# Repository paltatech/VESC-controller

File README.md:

# 3 phase motor controller for high power systems
This is the hardware repository of a 3 phase inverter brain, UNTESTED but designed with the following specs in mind:

* Compatible with VESC firmware and software tools
* Embedded security features (overcurrent protection, pwm overlap elimination, etc)

## Microcontroller
The core of the system is a 32 bit ARM Cortex M4 MCU (STM32F405) running ChibiOS RTOS.

## Communication interfaces
* CAN bus for control, configuration and monitoring
* USB for light usage, firmware upload/upgrade and configuration.
* UART, I2C and ADCs and GPIOs available

## Motor inputs
* Bus Voltage (differential)
* Phase current (differential)
* Phase voltage (differential)
* Gate driver fault
* Power_good from gate driver
* Motor temperature
* Hall/encoder
* Resolver

## Gate driver outputs
* PWM high/low
* dynamic gate drive current (pwm)
* 24v power

You can also check the layout [here](https://eyrie.io/board/6f397be723754f039735d8350260c2c0) 

Made open source with KiCAD, an open source EDA tool.

## Interface boards
This controller can be interfaced directly to a power stage, or through an interface board.
An example of interface board is at adaptor boards/power_integrations_2SP0115T2A/ and looks like this

An example of system assembly is also included in this repository

## Control board setup

First you need to flash the VESC bootloader. To do so, connect a STLinkv2 to connector J9. In a Linux machine open a terminal and clone the bootloader repository:

1. `git clone git@github.com:vedderb/bldc-bootloader.git`
2. `cd bldc-bootloader`
3. `make upload`   <- this will compile and flash the bootloader

Next step is to flash the VESC firmware.

1. `git clone git@github.com:vedderb/bldc.git`
2. `Make sure you go to conf_general.h and uncomment the line #define HW_VERSION_PALTA. This will enable all the features especific to this high power control board.`
3. `Configure the DEADTIME required for your power switches, look for the line #define HW_DEAD_TIME_VALUE		181  // 1.4usec  in hw_palta.h`
4. `cd bldc`
5. `make upload`  <- this will compile and flash vesc firmware

Connect the board via USB (conn J4) and launch the latest [VESC-tool](http://vesc-project.com/vesc_tool).

1. Press the connect button (top right). The status bar should show your PALTA board connected.
2. Load a sample configuration for this board, you probably need to tune the deadtime compensation field.
3. Run the motor setup wizard.

## System setup

A high power controller would generally need a battery, wiring, contactor, DC link, gate drivers, switches, an interface board, 3 current sensors, a heatsink and a motor. Make sure you have everything you need and you understand all the connections and dangers involved, especially the safety related stuff.

## License
This documentation describes Open Hardware and is licensed under the CERN OHL v. 1.2

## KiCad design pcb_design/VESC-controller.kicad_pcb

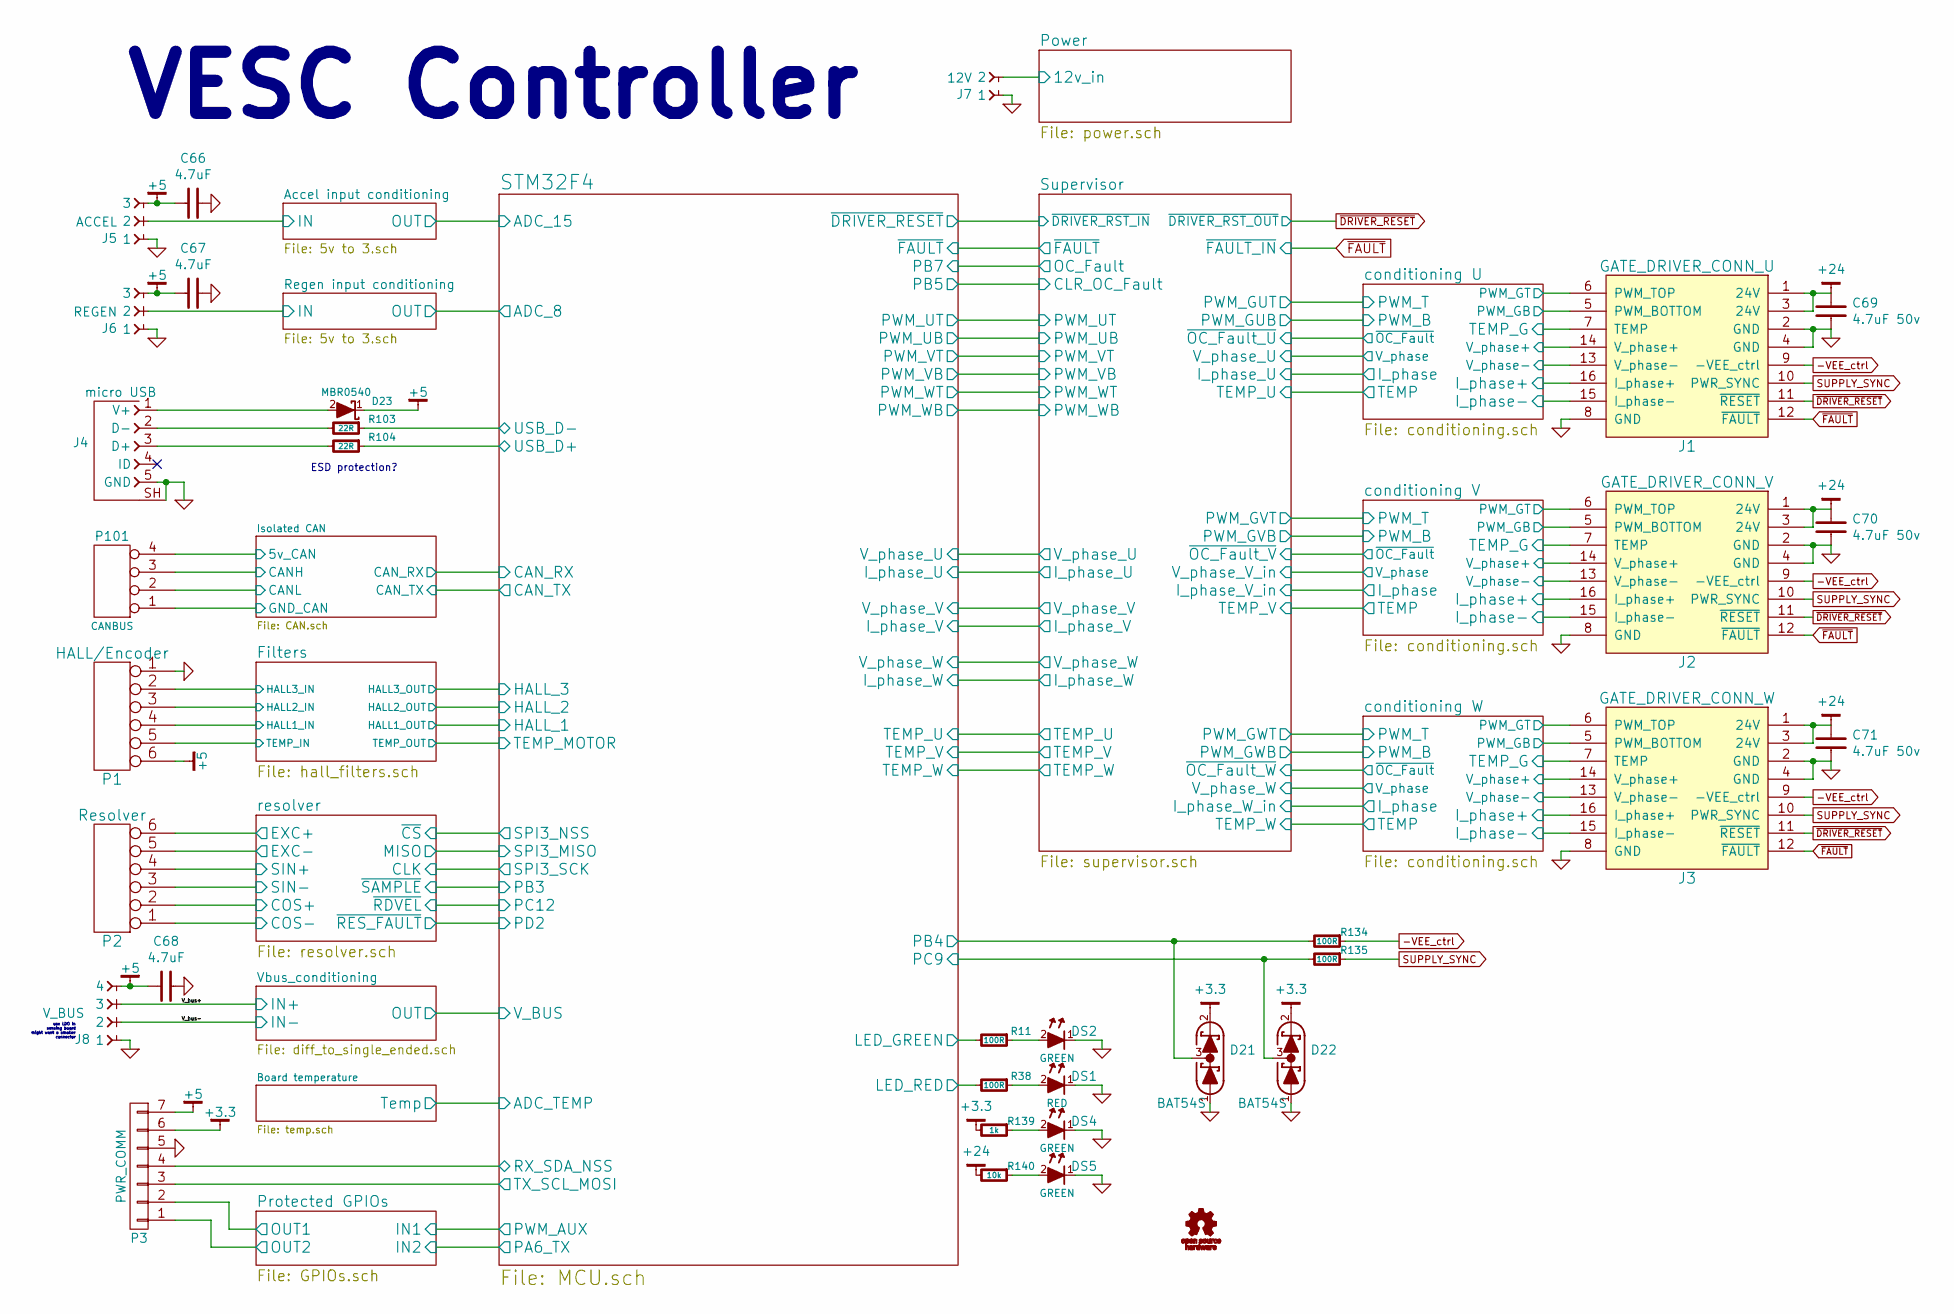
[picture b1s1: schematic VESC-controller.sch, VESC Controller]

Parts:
C66, C67, C68: 4.7uF; CAPC2012X70; MPN GRM21BR71A475KA73K
C69, C70, C71: 4.7uF 50v; CAPC3216X70; MPN GRM31CR71H475KA12L
D21, D22: BAT54S; SOT-23; mfg# TBAT54S,LM
D23: MBR0540; SOD-123; MPN MBR0540
DS1: RED; LED-0603; MPN LTST-C191KRKT
DS2, DS4, DS5: GREEN; LED-0603; MPN LTST-C191KGKT
J1: GATE_DRIVER_CONN_U; CONN-100MIL-M-2x8; MPN 67997-216HLF
J2: GATE_DRIVER_CONN_V; CONN-100MIL-M-2x8; MPN 67997-216HLF
J3: GATE_DRIVER_CONN_W; CONN-100MIL-M-2x8; MPN 67997-216HLF
J4: micro USB; CONN-10118194-0001LF-FCI; mfg# 10118194-0001LF
J5: ACCEL; mcv_1,5-3-G-3,81; MPN 1803439
J6: REGEN; mcv_1,5-3-G-3,81; MPN 1803439
J7: 12V; mcv_1,5-2-G-3,81; MPN 1803426
J8: V_BUS; mcv_1,5-4-G-3,81; MPN 1803442
P1: HALL/Encoder; mcv_1,5-6-G-3,81; MPN 1803468
P2: Resolver; mcv_1,5-6-G-3,81; MPN 1803468
P3: PWR_COMM; mcv_1,5-7-G-3,81; MPN 1803471
P101: CANBUS; b4b-ph-kl; MPN B4B-PH-K-S(LF)(SN)
R11, R38, R134, R135: 100R; RESC1608X50; MPN RC0603FR-07100RL
R103, R104: 22R; RESC1608X50; MPN RC0603FR-0722RL
R139: 1k; RESC1608X50; MPN RC0603FR-071KL
R140: 10k; RESC1608X50; MPN RC0603FR-0710KL

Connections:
+3.3: D21.2 (K), D22.2 (K), P3.6, R139.2; also elsewhere on the board
-VEE_ctrl: J1.9 (-VEE_ctrl), J2.9 (-VEE_ctrl), J3.9 (-VEE_ctrl), R134.1
/Accel input conditioning/IN: J5.2; also elsewhere on the board
/Filters/HALL1_IN: P1.4; also elsewhere on the board
/Filters/HALL2_IN: P1.3; also elsewhere on the board
/Filters/HALL3_IN: P1.2; also elsewhere on the board
/Filters/TEMP_IN: P1.5; also elsewhere on the board
/Isolated CAN/5v_CAN: P101.4; also elsewhere on the board
/Isolated CAN/CANH: P101.3; also elsewhere on the board
/Isolated CAN/CANL: P101.2; also elsewhere on the board
/Isolated CAN/GND_CAN: P101.1; also elsewhere on the board
/Power/12v_in: J7.2; also elsewhere on the board
/Protected GPIOs/OUT1: P3.2; also elsewhere on the board
/Protected GPIOs/OUT2: P3.1; also elsewhere on the board
/Regen input conditioning/IN: J6.2; also elsewhere on the board
/STM32F4/LED_GREEN: R11.2; also elsewhere on the board
/STM32F4/LED_RED: R38.2; also elsewhere on the board
/STM32F4/PB4: D21.3 (COM), R134.2; also elsewhere on the board
/STM32F4/PC9: D22.3 (COM), R135.2; also elsewhere on the board
/STM32F4/RX_SDA_NSS: P3.4; also elsewhere on the board
/STM32F4/TX_SCL_MOSI: P3.3; also elsewhere on the board
/STM32F4/USB_D+: R104.1; also elsewhere on the board
/STM32F4/USB_D-: R103.1; also elsewhere on the board
/V_bus+: J8.3; also elsewhere on the board
/V_bus-: J8.2; also elsewhere on the board
/conditioning U/I_phase+: J1.16 (I_phase+); also elsewhere on the board
/conditioning U/I_phase-: J1.15 (I_phase-); also elsewhere on the board
/conditioning U/PWM_GB: J1.5 (PWM_BOTTOM); also elsewhere on the board
/conditioning U/PWM_GT: J1.6 (PWM_TOP); also elsewhere on the board
/conditioning U/TEMP_G: J1.7 (TEMP); also elsewhere on the board
/conditioning U/V_phase+: J1.14 (V_phase+); also elsewhere on the board
/conditioning U/V_phase-: J1.13 (V_phase-); also elsewhere on the board
/conditioning V/I_phase+: J2.16 (I_phase+); also elsewhere on the board
/conditioning V/I_phase-: J2.15 (I_phase-); also elsewhere on the board
/conditioning V/PWM_GB: J2.5 (PWM_BOTTOM); also elsewhere on the board
/conditioning V/PWM_GT: J2.6 (PWM_TOP); also elsewhere on the board
/conditioning V/TEMP_G: J2.7 (TEMP); also elsewhere on the board
/conditioning V/V_phase+: J2.14 (V_phase+); also elsewhere on the board
/conditioning V/V_phase-: J2.13 (V_phase-); also elsewhere on the board
/conditioning W/I_phase+: J3.16 (I_phase+); also elsewhere on the board
/conditioning W/I_phase-: J3.15 (I_phase-); also elsewhere on the board
/conditioning W/PWM_GB: J3.5 (PWM_BOTTOM); also elsewhere on the board
/conditioning W/PWM_GT: J3.6 (PWM_TOP); also elsewhere on the board
/conditioning W/TEMP_G: J3.7 (TEMP); also elsewhere on the board
/conditioning W/V_phase+: J3.14 (V_phase+); also elsewhere on the board
/conditioning W/V_phase-: J3.13 (V_phase-); also elsewhere on the board
/resolver/COS+: P2.2; also elsewhere on the board
/resolver/COS-: P2.1; also elsewhere on the board
/resolver/EXC+: P2.6; also elsewhere on the board
/resolver/EXC-: P2.5; also elsewhere on the board
/resolver/SIN+: P2.4; also elsewhere on the board
/resolver/SIN-: P2.3; also elsewhere on the board
unnamed: D23.2 (A), J4.1 (V+)
unnamed: DS1.2 (A), R38.1
unnamed: DS2.2 (A), R11.1
unnamed: DS4.2 (A), R139.1
unnamed: DS5.2 (A), R140.1
unnamed: J4.2 (D-), R103.2
unnamed: J4.3 (D+), R104.2
SUPPLY_SYNC: J1.10 (PWR_SYNC), J2.10 (PWR_SYNC), J3.10 (PWR_SYNC), R135.1
~DRIVER_RESET: J1.11 (~RESET), J2.11 (~RESET), J3.11 (~RESET); also elsewhere on the board
~FAULT: J1.12 (~FAULT), J2.12 (~FAULT), J3.12 (~FAULT); also elsewhere on the board

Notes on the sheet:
ESD protection?
VESC Controller
use LDO in sensing board might want a smaller connector

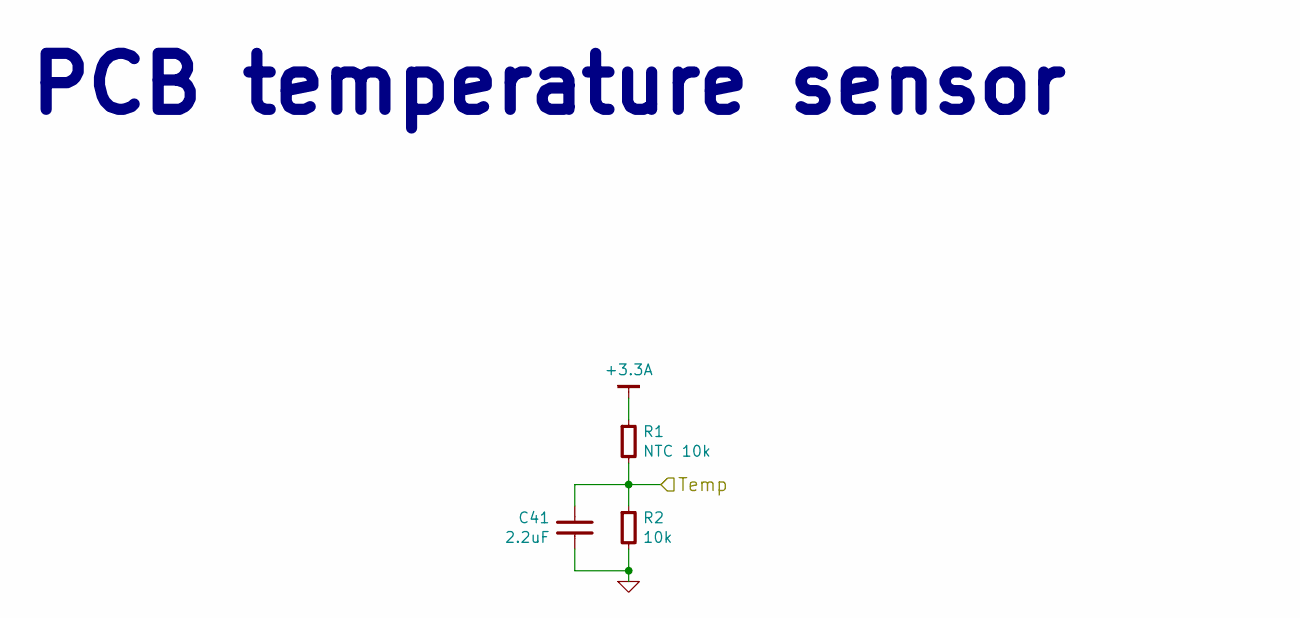
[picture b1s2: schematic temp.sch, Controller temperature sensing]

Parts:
C41: 2.2uF; CAPC1608X55; MPN GRM188R71A225KE15D
R1: NTC 10k; RESC1608X50; MPN NCP18XH103F03RB
R2: 10k; RESC1608X50; MPN RC0603FR-0710KL

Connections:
+3.3A: R1.1; also elsewhere on the board
/STM32F4/ADC_TEMP: C41.1, R1.2, R2.1; also elsewhere on the board

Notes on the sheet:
PCB temperature sensor

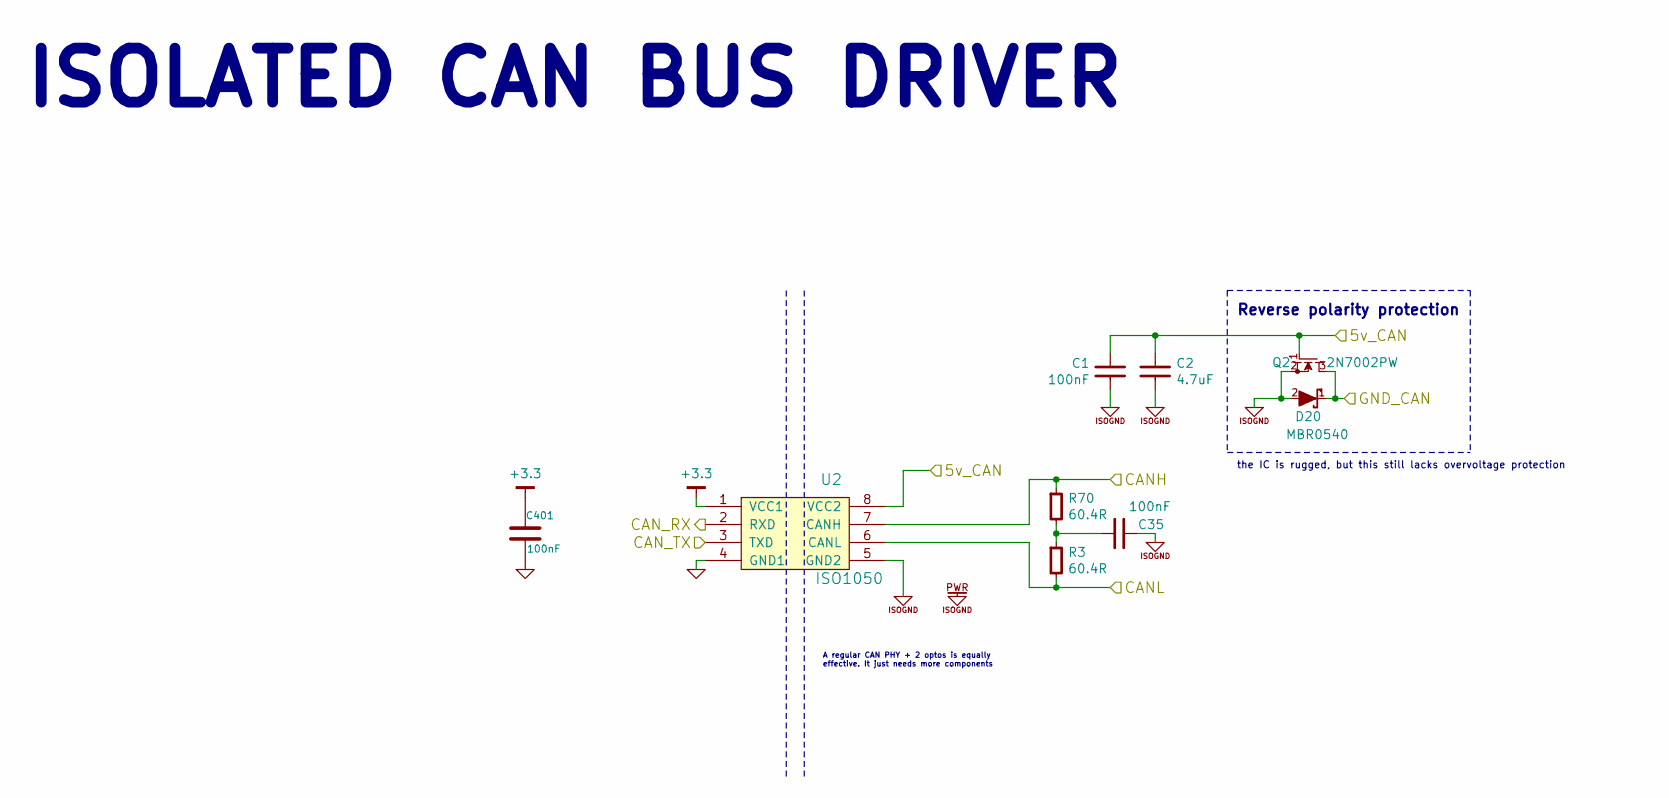
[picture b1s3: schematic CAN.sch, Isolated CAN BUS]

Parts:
C1, C35, C401: 100nF; CAPC1608X55; MPN GRM188R71E104KA01D
C2: 4.7uF; CAPC2012X70; MPN GRM21BR71A475KA73K
D20: MBR0540; SOD-123; MPN MBR0540
Q2: 2N7002PW; SC-70; mfg# 2N7002PW,115
R3, R70: 60.4R; RESC1608X50; MPN RC0603FR-0760R4L
U2: ISO1050; SO8-ISO1050; mfg# ISO1050DUBR

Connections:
+3.3: C401.1, U2.1 (VCC1); also elsewhere on the board
/Isolated CAN/5v_CAN: C1.1, C2.1, Q2.1 (G), U2.8 (VCC2); also elsewhere on the board
/Isolated CAN/CANH: R70.1, U2.7 (CANH); also elsewhere on the board
/Isolated CAN/CANL: R3.2, U2.6 (CANL); also elsewhere on the board
/Isolated CAN/CAN_RX: U2.2 (RXD); also elsewhere on the board
/Isolated CAN/CAN_TX: U2.3 (TXD); also elsewhere on the board
/Isolated CAN/GND_CAN: D20.1 (K), Q2.3 (D); also elsewhere on the board
ISOGND: C1.2, C2.2, C35.1, D20.2 (A), Q2.2 (S), U2.5 (GND2)
unnamed: C35.2, R3.1, R70.2

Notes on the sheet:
ISOLATED CAN BUS DRIVER
Reverse polarity protection
the IC is rugged, but this still lacks overvoltage protection
A regular CAN PHY + 2 optos is equally effective. It just needs more components

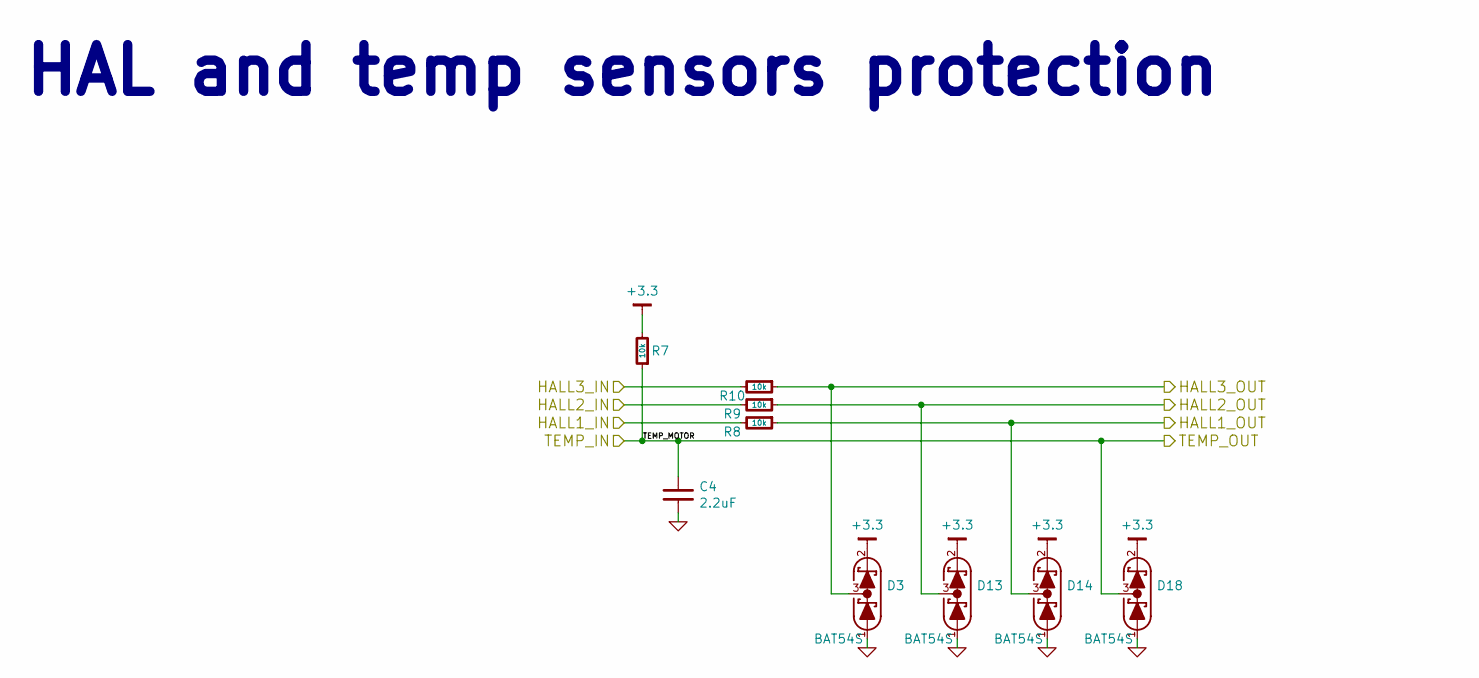
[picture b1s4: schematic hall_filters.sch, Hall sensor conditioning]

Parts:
C4: 2.2uF; CAPC1608X55; MPN GRM188R71A225KE15D
D3, D13, D14, D18: BAT54S; SOT-23; mfg# TBAT54S,LM
R7, R8, R9, R10: 10k; RESC1608X50; MPN RC0603FR-0710KL

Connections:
+3.3: D3.2 (K), D13.2 (K), D14.2 (K), D18.2 (K), R7.2; also elsewhere on the board
/Filters/HALL1_IN: R8.2; also elsewhere on the board
/Filters/HALL1_OUT: D14.3 (COM), R8.1; also elsewhere on the board
/Filters/HALL2_IN: R9.2; also elsewhere on the board
/Filters/HALL2_OUT: D13.3 (COM), R9.1; also elsewhere on the board
/Filters/HALL3_IN: R10.2; also elsewhere on the board
/Filters/HALL3_OUT: D3.3 (COM), R10.1; also elsewhere on the board
/Filters/TEMP_IN: C4.1, D18.3 (COM), R7.1; also elsewhere on the board

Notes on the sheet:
HAL and temp sensors protection

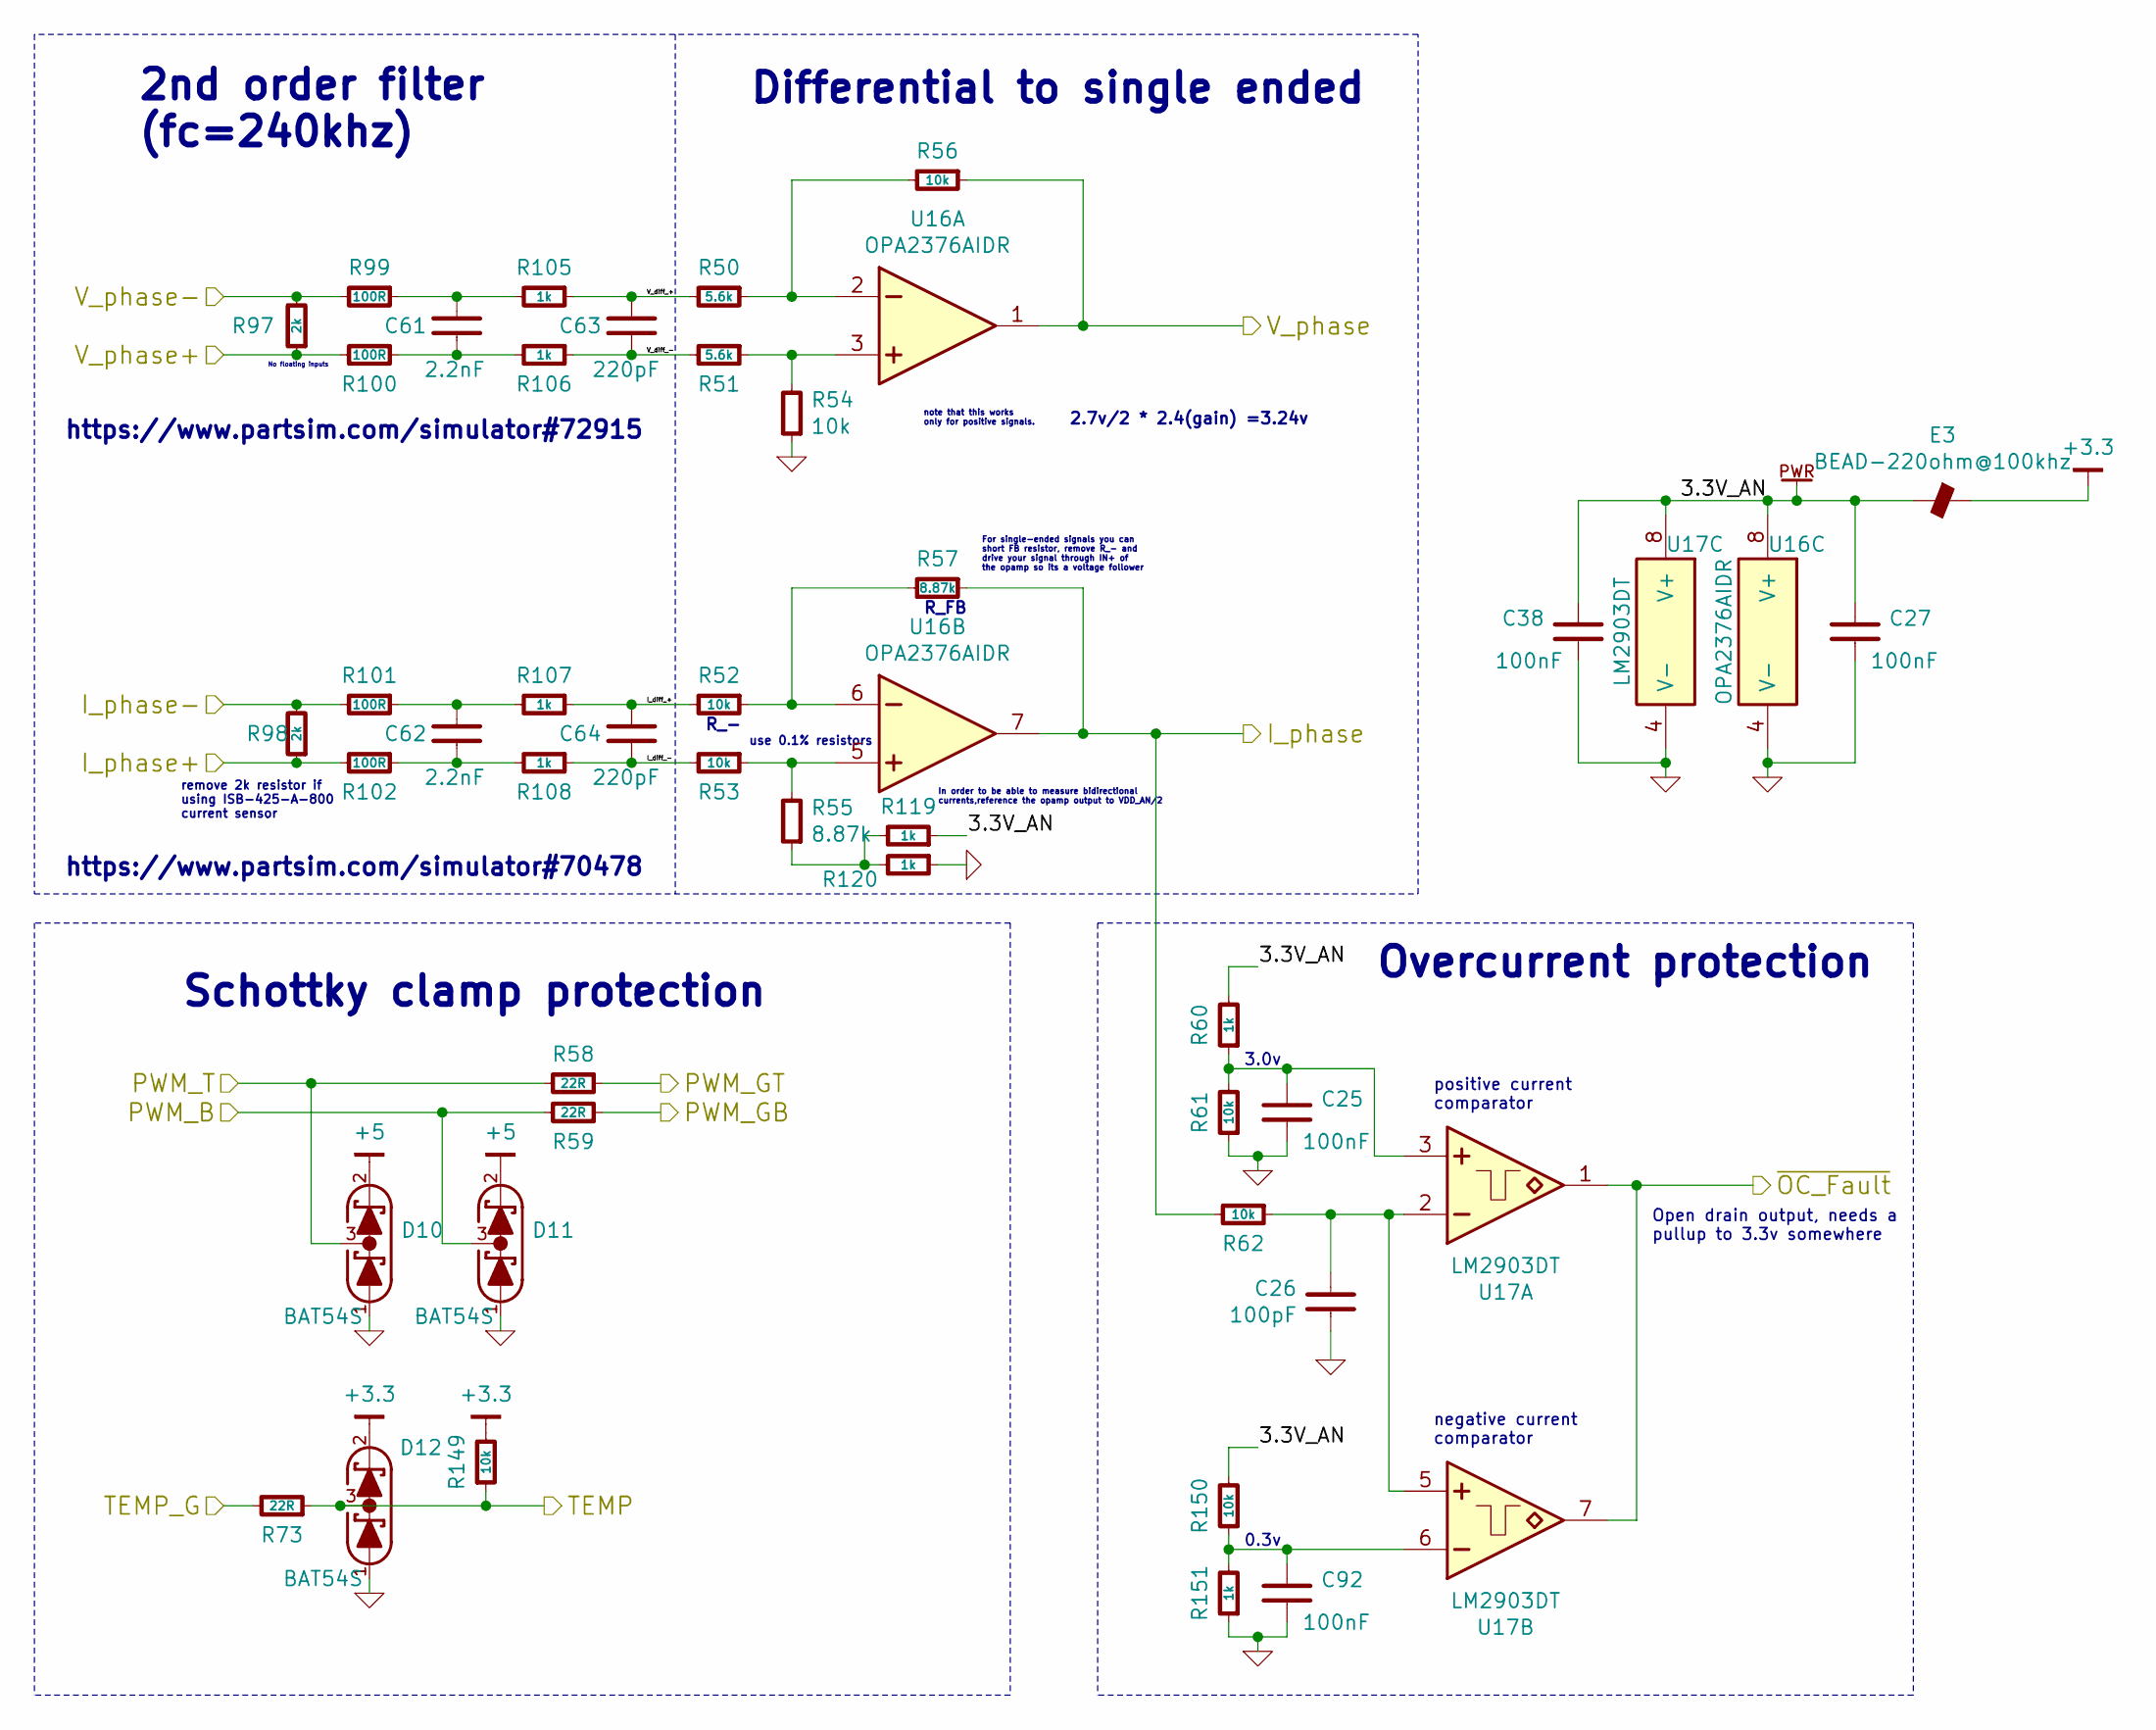
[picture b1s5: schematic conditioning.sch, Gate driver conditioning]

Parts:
C3, C9, C36, C90: 100nF; CAPC1608X55; MPN GRM188R71E104KA01D
C8: 100pF; CAPC1608X55; MPN C0603C101J5GACTU
C53, C54: 2.2nF; CAPC1608X55
C55, C56: 220pF; CAPC1608X55; MPN GRM1885C1H221JA01D
D4, D5, D6: BAT54S; SOT-23; mfg# TBAT54S,LM
E1: BEAD-220ohm@100khz; INDC2012X130; MPN BLM21PG221SN1D
R4, R5: 5.6k; RESC1608X50; MPN RC0603FR-078K87L
R6, R14, R15, R16, R18, R24, R25, R144: 10k; RESC1608X50; MPN RC0603FR-0710KL
R17, R19: 8.87k; RESC1608X50; MPN RC0603FR-0710KL
R20, R21, R71: 22R; RESC1608X50; MPN RC0603FR-0722RL
R23, R82, R83, R84, R85, R115, R116, R145: 1k; RESC1608X50; MPN RC0603FR-071KL
R76, R77: 2k; RESC1608X50; MPN RC0603FR-072KL
R78, R79, R80, R81: 100R; RESC1608X50; MPN RC0603FR-07100RL
U3: OPA2376AIDR; SOIC127P600X175-8; mfg# OPA2376AIDR
U4: LM2903DT; SOIC127P600X175-8; mfg# LM2903DT

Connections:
+3.3: D6.2 (K), E1.2, R6.2; also elsewhere on the board
/Supervisor/PWM_GUT: D4.3 (COM), R20.2; also elsewhere on the board
/conditioning U/3.3V_AN: C9.1, C36.1, E1.1, R23.2, R115.1, R144.2, U3.8 (V+), U4.8 (V+)
/conditioning U/I_diff_+: C56.1, R14.2, R84.1
/conditioning U/I_diff_-: C56.2, R15.2, R85.1
/conditioning U/I_phase: R19.1, R25.2, U3.7 (OUT); also elsewhere on the board
/conditioning U/I_phase+: R77.1, R81.2; also elsewhere on the board
/conditioning U/I_phase-: R77.2, R80.2; also elsewhere on the board
/conditioning U/PWM_B: D5.3 (COM), R21.2; also elsewhere on the board
/conditioning U/PWM_GB: R21.1; also elsewhere on the board
/conditioning U/PWM_GT: R20.1; also elsewhere on the board
/conditioning U/TEMP: D6.3 (COM), R6.1, R71.1; also elsewhere on the board
/conditioning U/TEMP_G: R71.2; also elsewhere on the board
/conditioning U/V_diff_+: C55.1, R4.2, R82.1
/conditioning U/V_diff_-: C55.2, R5.2, R83.1
/conditioning U/V_phase: R18.1, U3.1 (OUT); also elsewhere on the board
/conditioning U/V_phase+: R76.1, R79.2; also elsewhere on the board
/conditioning U/V_phase-: R76.2, R78.2; also elsewhere on the board
/conditioning U/~OC_Fault: U4.1 (OUT), U4.7 (OUT); also elsewhere on the board
unnamed: C3.1, R23.1, R24.2, U4.3 (IN+)
unnamed: C8.1, R25.1, U4.2 (IN-), U4.5 (IN+)
unnamed: C53.1, R78.1, R82.2
unnamed: C53.2, R79.1, R83.2
unnamed: C54.1, R80.1, R84.2
unnamed: C54.2, R81.1, R85.2
unnamed: C90.1, R144.1, R145.2, U4.6 (IN-)
unnamed: R14.1, R19.2, U3.6 (IN-)
unnamed: R15.1, R17.2, U3.5 (IN+)
unnamed: R5.1, R16.2, U3.3 (IN+)
unnamed: R4.1, R18.2, U3.2 (IN-)
unnamed: R17.1, R115.2, R116.2

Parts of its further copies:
C22, C24, C25, C27, C37, C38, C91, C92: 100nF; CAPC1608X55; MPN GRM188R71E104KA01D
C23, C26: 100pF; CAPC1608X55; MPN C0603C101J5GACTU
C57, C58, C61, C62: 2.2nF; CAPC1608X55
C59, C60, C63, C64: 220pF; CAPC1608X55; MPN GRM1885C1H221JA01D
D7, D8, D9, D10, D11, D12: BAT54S; SOT-23; mfg# TBAT54S,LM
E2, E3: BEAD-220ohm@100khz; INDC2012X130; MPN BLM21PG221SN1D
R34, R35, R50, R51: 5.6k; RESC1608X50; MPN RC0603FR-078K87L
R36, R39, R40, R42, R47, R48, R52, R53, R54, R56, R61, R62, R146, R147, R149, R150: 10k; RESC1608X50; MPN RC0603FR-0710KL
R41, R43, R55, R57: 8.87k; RESC1608X50; MPN RC0603FR-0710KL
R44, R45, R58, R59, R72, R73: 22R; RESC1608X50; MPN RC0603FR-0722RL
R46, R60, R93, R94, R95, R96, R105, R106, R107, R108, R117, R118, R119, R120, R148, R151: 1k; RESC1608X50; MPN RC0603FR-071KL
R87, R88, R97, R98: 2k; RESC1608X50; MPN RC0603FR-072KL
R89, R90, R91, R92, R99, R100, R101, R102: 100R; RESC1608X50; MPN RC0603FR-07100RL
U10, U17: LM2903DT; SOIC127P600X175-8; mfg# LM2903DT
U12, U16: OPA2376AIDR; SOIC127P600X175-8; mfg# OPA2376AIDR

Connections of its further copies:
+3.3: D9.2 (K), D12.2 (K), E2.2, E3.2, R146.2, R149.2; also elsewhere on the board
/Supervisor/PWM_GVT: D7.3 (COM), R44.2; also elsewhere on the board
/Supervisor/PWM_GWT: D10.3 (COM), R58.2; also elsewhere on the board
/conditioning U/~OC_Fault: U10.1 (OUT), U10.7 (OUT), U17.1 (OUT), U17.7 (OUT); also elsewhere on the board
/conditioning V/3.3V_AN: C24.1, C37.1, E2.1, R46.2, R117.1, R147.2, U10.8 (V+), U12.8 (V+)
/conditioning V/I_diff_+: C60.1, R36.2, R95.1
/conditioning V/I_diff_-: C60.2, R39.2, R96.1
/conditioning V/I_phase: R43.1, R48.2, U12.7 (OUT); also elsewhere on the board
/conditioning V/I_phase+: R88.1, R92.2; also elsewhere on the board
/conditioning V/I_phase-: R88.2, R91.2; also elsewhere on the board
/conditioning V/PWM_B: D8.3 (COM), R45.2; also elsewhere on the board
/conditioning V/PWM_GB: R45.1; also elsewhere on the board
/conditioning V/PWM_GT: R44.1; also elsewhere on the board
/conditioning V/TEMP: D9.3 (COM), R72.1, R146.1; also elsewhere on the board
/conditioning V/TEMP_G: R72.2; also elsewhere on the board
/conditioning V/V_diff_+: C59.1, R34.2, R93.1
/conditioning V/V_diff_-: C59.2, R35.2, R94.1
/conditioning V/V_phase: R42.1, U12.1 (OUT); also elsewhere on the board
/conditioning V/V_phase+: R87.1, R90.2; also elsewhere on the board
/conditioning V/V_phase-: R87.2, R89.2; also elsewhere on the board
/conditioning W/3.3V_AN: C27.1, C38.1, E3.1, R60.2, R119.1, R150.2, U16.8 (V+), U17.8 (V+)
/conditioning W/I_diff_+: C64.1, R52.2, R107.1
/conditioning W/I_diff_-: C64.2, R53.2, R108.1
/conditioning W/I_phase: R57.1, R62.2, U16.7 (OUT); also elsewhere on the board
/conditioning W/I_phase+: R98.1, R102.2; also elsewhere on the board
/conditioning W/I_phase-: R98.2, R101.2; also elsewhere on the board
/conditioning W/PWM_B: D11.3 (COM), R59.2; also elsewhere on the board
/conditioning W/PWM_GB: R59.1; also elsewhere on the board
/conditioning W/PWM_GT: R58.1; also elsewhere on the board
/conditioning W/TEMP: D12.3 (COM), R73.1, R149.1; also elsewhere on the board
/conditioning W/TEMP_G: R73.2; also elsewhere on the board
/conditioning W/V_diff_+: C63.1, R50.2, R105.1
/conditioning W/V_diff_-: C63.2, R51.2, R106.1
/conditioning W/V_phase: R56.1, U16.1 (OUT); also elsewhere on the board
/conditioning W/V_phase+: R97.1, R100.2; also elsewhere on the board
/conditioning W/V_phase-: R97.2, R99.2; also elsewhere on the board
unnamed: C22.1, R46.1, R47.2, U10.3 (IN+)
unnamed: C23.1, R48.1, U10.2 (IN-), U10.5 (IN+)
unnamed: C25.1, R60.1, R61.2, U17.3 (IN+)
unnamed: C26.1, R62.1, U17.2 (IN-), U17.5 (IN+)
unnamed: C57.1, R89.1, R93.2
unnamed: C57.2, R90.1, R94.2
unnamed: C58.1, R91.1, R95.2
unnamed: C58.2, R92.1, R96.2
unnamed: C61.1, R99.1, R105.2
unnamed: C61.2, R100.1, R106.2
unnamed: C62.1, R101.1, R107.2
unnamed: C62.2, R102.1, R108.2
unnamed: C91.1, R147.1, R148.2, U10.6 (IN-)
unnamed: C92.1, R150.1, R151.2, U17.6 (IN-)
unnamed: R34.1, R42.2, U12.2 (IN-)
unnamed: R35.1, R40.2, U12.3 (IN+)
unnamed: R36.1, R43.2, U12.6 (IN-)
unnamed: R39.1, R41.2, U12.5 (IN+)
unnamed: R50.1, R56.2, U16.2 (IN-)
unnamed: R51.1, R54.2, U16.3 (IN+)
unnamed: R52.1, R57.2, U16.6 (IN-)
unnamed: R53.1, R55.2, U16.5 (IN+)
unnamed: R41.1, R117.2, R118.2
unnamed: R55.1, R119.2, R120.2

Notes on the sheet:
Overcurrent protection
Differential to single ended
Schottky clamp protection
2nd order filter (fc=240khz)
No floating inputs
note that this works only for positive signals.
In order to be able to measure bidirectional currents,reference the opamp output to VDD_AN/2
For single-ended signals you can short FB resistor, remove R_- and drive your signal through IN+ of the opamp so its a voltage follower
R_FB
R_-
https://www.partsim.com/simulator#70478
2.7v/2 * 2.4(gain) =3.24v
https://www.partsim.com/simulator#72915
use 0.1% resistors
remove 2k resistor if using ISB-425-A-800 current sensor
positive current comparator
negative current comparator
0.3v
3.0v
Open drain output, needs a pullup to 3.3v somewhere

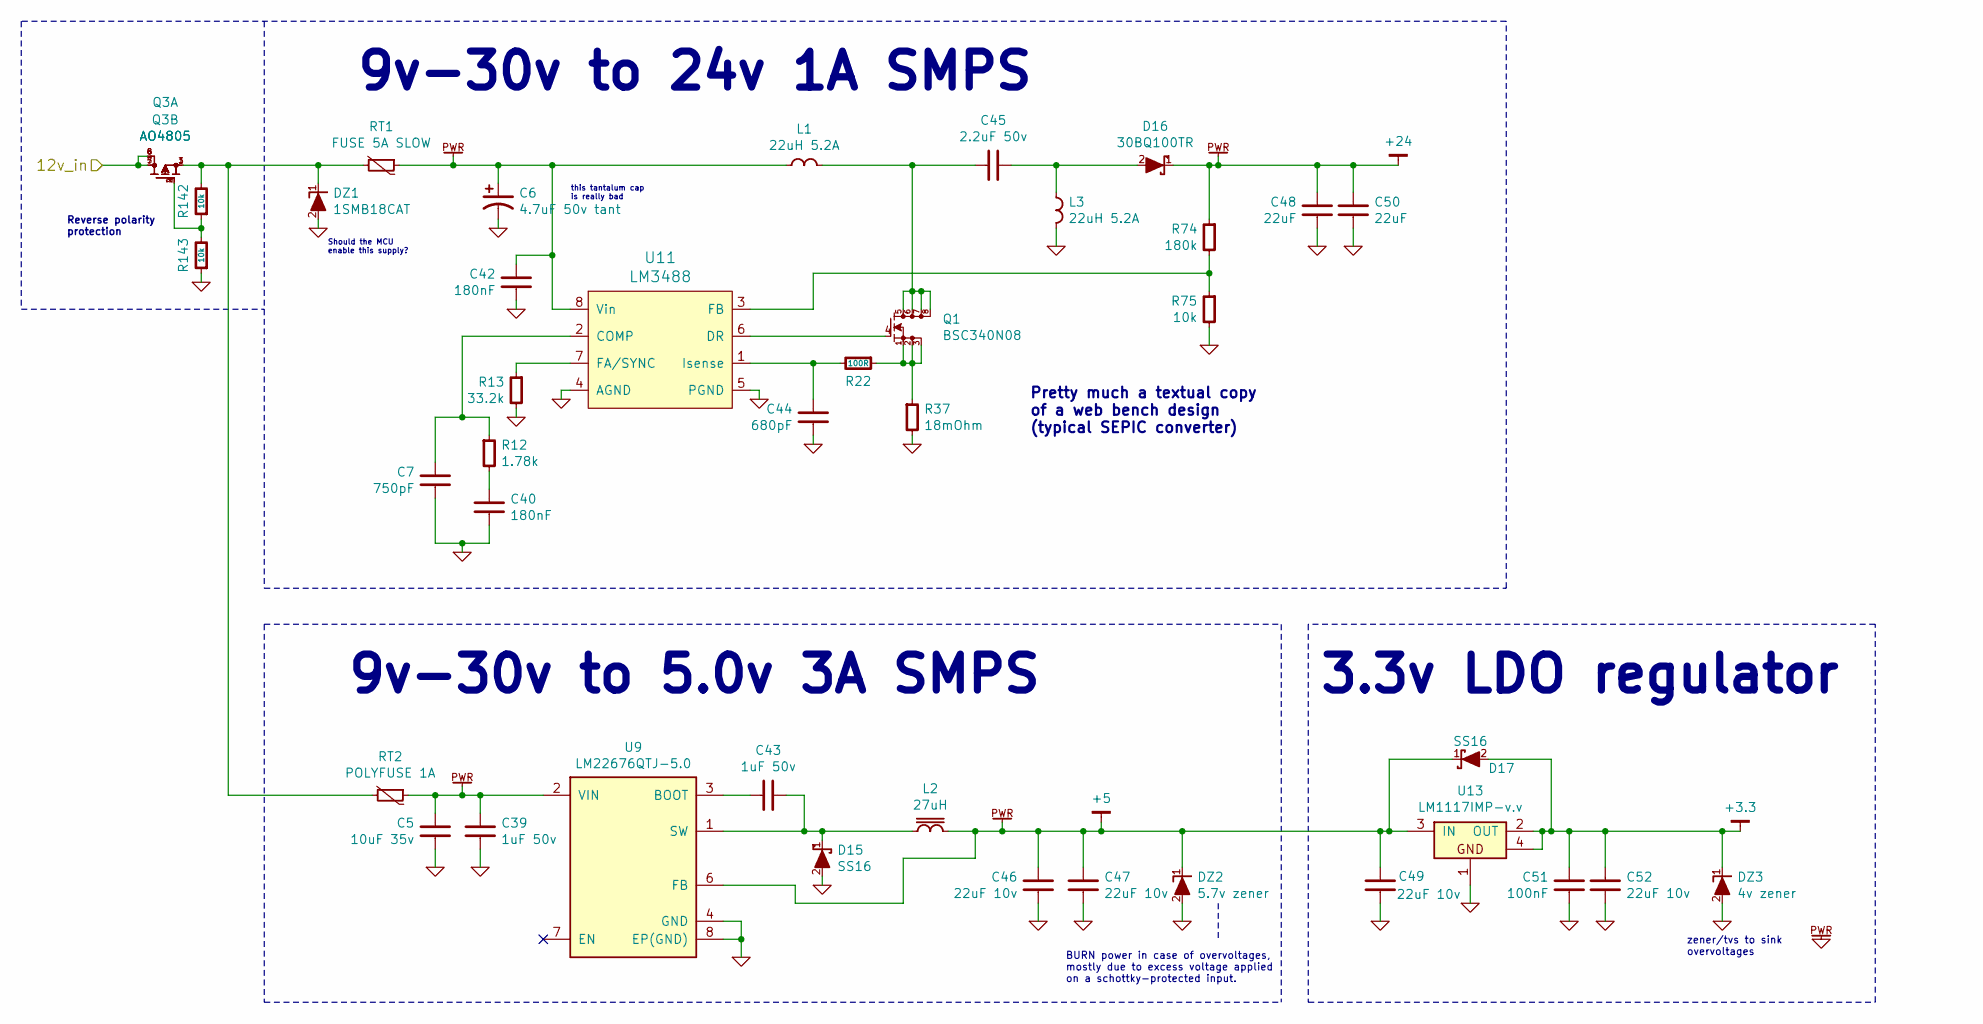
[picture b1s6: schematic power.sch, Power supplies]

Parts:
C5: 10uF 35v; CAPC3216X70; MPN GMK316AB7106KL-TR
C6: 4.7uF 50v tant; CAPMP7343X310; mfg# 593D475X9050D2TE3
C7: 750pF; CAPC2012X70; mfg# CL21C751JBCNNNC
C39, C43: 1uF 50v; CAPC2012X70; MPN UMK212B7105KG-T
C40, C42: 180nF; CAPC1608X55; MPN GRM188R71E184KA88D
C44: 680pF; CAPC2012X70; mfg# CL21C751JBCNNNC
C45: 2.2uF 50v; CAPC3216X70; mfg# GRM31CR71H225KA88L
C46, C47, C49, C52: 22uF 10v; CAPC3216X70; mfg# LMK316AB7226ML-TR
C48, C50: 22uF; CAPC2012X70; mfg# C2012X5R1V226M125AC
C51: 100nF; CAPC1608X55; MPN GRM188R71E104KA01D
D15, D17: SS16; DIOM5326X292; MPN SS16
D16: 30BQ100TR; DIOM7959X265; mfg# 30BQ100TR
DZ1: 1SMB18CAT; do214aa; mfg# 1SMB18CAT3GOSCT-ND
DZ2: 5.7v zener; DIOM5226X203; MPN 1SMA59xxBT3G
DZ3: 4v zener; DIOM5226X203
L1, L3: 22uH 5.2A; BOURNS-SRR1210; mfg# SRR1210-220M
L2: 27uH; BOURNS-SDR1307; mfg# SDR1307-270ML
Q1: BSC340N08; TEXAS-Q5A; mfg# BSC340N08NS3GATMA1
Q3: AO4805; SOIC127P600X175-8; MPN AO4805
R12: 1.78k; RESC1608X50; MPN RC0603FR-071K78L
R13: 33.2k; RESC1608X50; MPN RC0603FR-0733K2L
R22: 100R; RESC1608X50; MPN RC0603FR-07100RL
R37: 18mOhm; CAPC1632X76; mfg# PRL1632-R018-F-T1
R74: 180k; RESC1608X50; MPN RC0603FR-07180KL
R75, R142, R143: 10k; RESC1608X50; MPN RC0603FR-0710KL
RT1: FUSE 5A SLOW; RESC3216X60; MPN C1S 5
RT2: POLYFUSE 1A; RESC3216X60; MPN 0ZCJ0050AF2E
U9: LM22676QTJ-5.0; TO-263-7-TEXAS; MPN LM22676QTJE-5.0/NOPB
U11: LM3488; SOP65P490X109-8; MPN LM3488MM/NOPB
U13: LM1117IMP-v.v; SOT-223; MPN LM1117IMP-3.3/NOPB

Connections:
+3.3: C51.1, C52.2, D17.2 (A), DZ3.1 (K), U13.2 (OUT), U13.4; also elsewhere on the board
/Power/12v_in: Q3.5 (D1A), Q3.6 (D1B), Q3.7 (D2A), Q3.8 (D2B); also elsewhere on the board
unnamed: C7.1, R12.1, U11.2 (COMP)
unnamed: C40.1, R12.2
unnamed: C43.1, D15.1 (K), L2.2, U9.1 (SW)
unnamed: C43.2, U9.3 (BOOT)
unnamed: C44.1, R22.2, U11.1 (Isense)
unnamed: C45.1, D16.2 (A), L3.2
unnamed: C45.2, L1.1, Q1.5 (D), Q1.6 (D), Q1.7 (D), Q1.8 (D)
unnamed: DZ1.1 (K), Q3.1 (S2), Q3.3 (S1), R142.2, RT1.2, RT2.2
unnamed: Q1.1 (S), Q1.2 (S), Q1.3 (S), R22.1, R37.1
unnamed: Q1.4 (G), U11.6 (DR)
unnamed: Q3.2 (G1), Q3.4 (G1), R142.1, R143.2
unnamed: R13.1, U11.7 (FA/SYNC)
unnamed: R74.2, R75.1, U11.3 (FB)

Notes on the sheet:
9v-30v to 24v 1A SMPS
Pretty much a textual copy of a web bench design (typical SEPIC converter)
9v-30v to 5.0v 3A SMPS
3.3v LDO regulator
Should the MCU enable this supply?
Reverse polarity protection
this tantalum cap is really bad
zener/tvs to sink overvoltages
BURN power in case of overvoltages, mostly due to excess voltage applied on a schottky-protected input.
